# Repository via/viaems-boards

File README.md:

# viaems-boards
ViaEMS PCB Designs

In order of creation...
## Analog V1
 - Analog/ADC Core board based on a DIP TLC2543
 - All throughhole
 - Dedicated 5V supply
 - 4 Thermistor inputs
 - Inputs for EGO, BRV, MAP, TPS
 - 5 Spares

## IO V1
 - IO core board
 - 4x ignition outputs
 - 6x Low side drivers
 - CAN driver
 - Digital inputs

Do not use because:
 - 3v supply for CAN doesn't work at all
 - the FETs without gate drivers has poor performance from a 3.3 V
   microcontroller
 - No VR inputs

## Viaems V1
Original all-in-one board for ViaEMS
 - STM32F407VGT
 - 8x Low side outputs (fed by gate drivers)
 - 4x ignition outputs
 - 2x High side drivers
 - Dedicated MAP and AAP sensors on-board
 - AD7888 SPI ADC with thermistor and core inputs, one spare
 - CAN driver

Shouldn't be used anymore, but really only because the outputs chosen for test
trigger vs real triggers are different in firmware.  The board can be used
again with some minor tweaks (and I have used this board for years)

## Analog V2
Experiment board to prototype use of the MAX11632, and some knock sensing
equipment.  The ADC samples fast enough to dedicate two inputs to knock sensing,
which uses an op amp input filter.  Provides core inputs, a dedicated MAP
sensor, and an additional 8 spare inputs.

The board works fine, but I'm unlikely to commit to the MAX11632: since it seems
incredibly finicky with SPI noise, and it doesn't provide a good way to know if
there is an issue. It requires a setup command.  The knock sensing filter works
great though.  Ultimately issues with this chip pushed me to investigate the
TLV2553.

Also, its way too big.

## IO V2
** Do not use! **
Simple breakout board as an upgrade to IO V2:
 - IO Core board
 - 5v supply (and fused output)
 - 4x ignition outputs
 - 8x Low Side drivers (including 4 injectors)
 - 2x Digital inputs
 - 2 VR inputs

Experiment with replacing the 2-port gate drivers with the 4-port MIC4469
 variant.  This board was made mostly to experiment with various FETs.

This board is missing inline resistors between the MIC4469 and FETs.  This is
incredibly important for the VND7NV04 -- without it, the negative pulse from
injectors destroys the gate control logic and causes it to latch partly on.

Ultimately this board is also *way* too big.

## Analog V3
Another experiment, this time for the TI TLV2553.  This ADC has only 11 inputs,
and samples at 200kHz (vs 300 kHz of the MAX11632).  However, its control is
identical to the TLC2543, which has self test functionality.  It is still fast
enough to allow for two inputs to be sampled at 40 kHz (and the rest at 10 kHz).
 - Analog Core board based on TLV2553
 - Small form factor (78x34 mm)
 - 2x SPI headers to make debugging easier
 - dedicated 5v supply (and fused output)
 - 1x MAP input
 - 2x knock sensor inputs
 - 3x Spare inputs

 I decided (after the fact) to make all the other boards the same form factor

## LSD V1 (Split from IO V2)
The full contents of IO V2 could not fit on a single 78x34 board, so it is split
into two -- one for the low side drivers, one for everything else.  Other
lessons learned from IO V2 were to add gate resistors for the FETs, and that
indicator LEDs are worth the effort to plan into the design.
 - Low side/Injector Core board
 - Small form factor (78x34)
 - 4x Injector outputs
 - 4x LSD outputs (or an extra 4x injectors)
 - Indicator LEDs

## Pwr-Ign-V1 (Split from IO V2)
An upgrade from IO V2, with gate resistors fixed, indicator LEDs on all outputs
and trigger inputs
 - 5v supply
 - 2x VR inputs
 - 2x Digital inputs
 - 4x Ignition outputs

## Proto-stm32f427 (v2)
Generic testing board for stm32f427 or gd32f470.  This is the same pcb
dimensions as the prior 3 boards, and comes with:
 - 100 LQFP footprint for microcontroller
 - USB Type-C (with FS-only pinout)
 - Optional soic-8 spi nor flash footprint on SPI1
 - Full 20 pin SWD+ETM trace connector

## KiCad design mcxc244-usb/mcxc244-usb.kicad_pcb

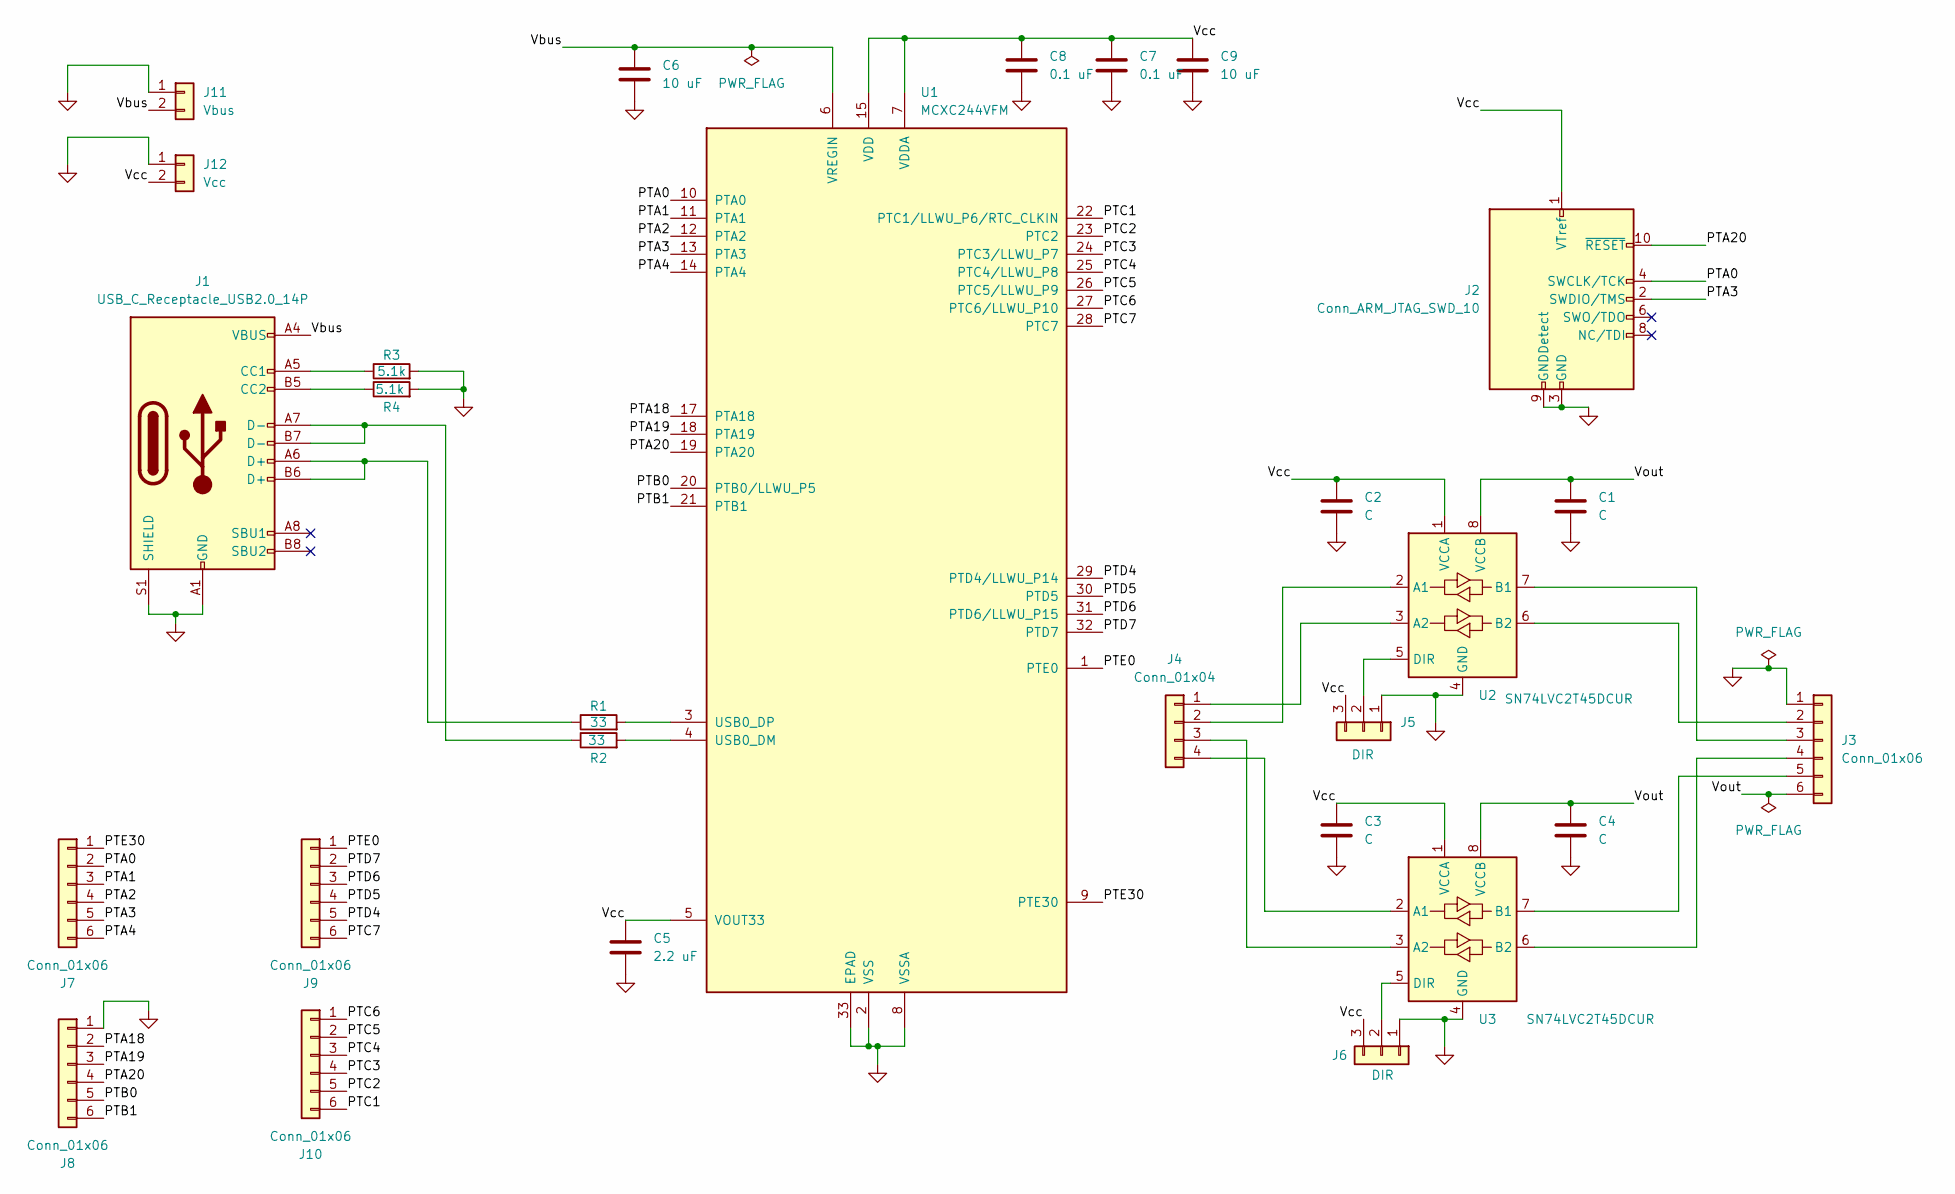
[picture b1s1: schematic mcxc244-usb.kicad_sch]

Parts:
C1, C2, C3, C4: C; C_0805_2012Metric
C5: 2.2 uF; C_0805_2012Metric
C6, C9: 10 uF; C_0805_2012Metric
C7, C8: 0.1 uF; C_0805_2012Metric
J1: USB_C_Receptacle_USB2.0_14P; USB_C_Receptacle_GCT_USB4105-xx-A_16P_TopMnt_Horizontal
J2: Conn_ARM_JTAG_SWD_10; PinHeader_2x05_P1.27mm_Vertical_SMD
J3, J7, J8, J9, J10: Conn_01x06; PinHeader_1x06_P2.54mm_Vertical
J4: Conn_01x04; PinHeader_1x04_P2.54mm_Vertical
J5, J6: DIR; PinHeader_1x03_P2.54mm_Vertical
J11: Vbus; PinHeader_1x02_P2.54mm_Vertical
J12: Vcc; PinHeader_1x02_P2.54mm_Vertical
R1, R2: 33; R_0805_2012Metric
R3, R4: 5.1k; R_0805_2012Metric
U1: MCXC244VFM; QFN-32-1EP_5x5mm_P0.5mm_EP3.45x3.45mm
U2, U3: SN74LVC2T45DCUR; VSSOP-8_2.3x2mm_P0.5mm

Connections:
/PTA0: J2.4 (SWCLK/TCK), J7.2, U1.10 (PTA0)
/PTA1: J7.3, U1.11 (PTA1)
/PTA2: J7.4, U1.12 (PTA2)
/PTA3: J2.2 (SWDIO/TMS), J7.5, U1.13 (PTA3)
/PTA4: J7.6, U1.14 (PTA4)
/PTA18: J8.2, U1.17 (PTA18)
/PTA19: J8.3, U1.18 (PTA19)
/PTA20: J2.10 (~RESET), J8.4, U1.19 (PTA20)
/PTB0: J8.5, U1.20 (PTB0/LLWU_P5)
/PTB1: J8.6, U1.21 (PTB1)
/PTC1: J10.6, U1.22 (PTC1/LLWU_P6/RTC_CLKIN)
/PTC2: J10.5, U1.23 (PTC2)
/PTC3: J10.4, U1.24 (PTC3/LLWU_P7)
/PTC4: J10.3, U1.25 (PTC4/LLWU_P8)
/PTC5: J10.2, U1.26 (PTC5/LLWU_P9)
/PTC6: J10.1, U1.27 (PTC6/LLWU_P10)
/PTC7: J9.6, U1.28 (PTC7)
/PTD4: J9.5, U1.29 (PTD4/LLWU_P14)
/PTD5: J9.4, U1.30 (PTD5)
/PTD6: J9.3, U1.31 (PTD6/LLWU_P15)
/PTD7: J9.2, U1.32 (PTD7)
/PTE0: J9.1, U1.1 (PTE0)
/PTE30: J7.1, U1.9 (PTE30)
/Vbus: C6.1, J1.A4 (VBUS), J1.A9 (VBUS), J1.B4 (VBUS), J1.B9 (VBUS), J11.2, U1.6 (VREGIN)
/Vcc: C2.1, C3.1, C5.1, C7.1, C8.1, C9.1, J2.1 (VTref), J5.3, J6.3, J12.2, U1.5 (VOUT33), U1.7 (VDDA), U1.15 (VDD), U2.1 (VCCA), U3.1 (VCCA)
/Vout: C1.1, C4.1, J3.6, U2.8 (VCCB), U3.8 (VCCB)
GND: C1.2, C2.2, C3.2, C4.2, C5.2, C6.2, C7.2, C8.2, C9.2, J1.A1 (GND), J1.A12 (GND), J1.B1 (GND), J1.B12 (GND), J1.S1 (SHIELD), J2.3 (GND), J2.5 (GND), J2.9 (GNDDetect), J3.1, J5.1, J6.1, J8.1, J11.1, J12.1, R3.2, R4.2, U1.2 (VSS), U1.8 (VSSA), U1.16 (VSS), U1.33 (EPAD), U2.4 (GND), U3.4 (GND)
unnamed: J1.A5 (CC1), R3.1
unnamed: J1.B5 (CC2), R4.1
unnamed: J1.A6 (D+), J1.B6 (D+), R1.1
unnamed: J1.A7 (D-), J1.B7 (D-), R2.1
unnamed: J3.2, U2.6 (B2)
unnamed: J3.3, U2.7 (B1)
unnamed: J3.4, U3.6 (B2)
unnamed: J3.5, U3.7 (B1)
unnamed: J4.1, U2.3 (A2)
unnamed: J4.2, U2.2 (A1)
unnamed: J4.3, U3.3 (A2)
unnamed: J4.4, U3.2 (A1)
unnamed: J5.2, U2.5 (DIR)
unnamed: J6.2, U3.5 (DIR)
unnamed: R2.2, U1.4 (USB0_DM)
unnamed: R1.2, U1.3 (USB0_DP)

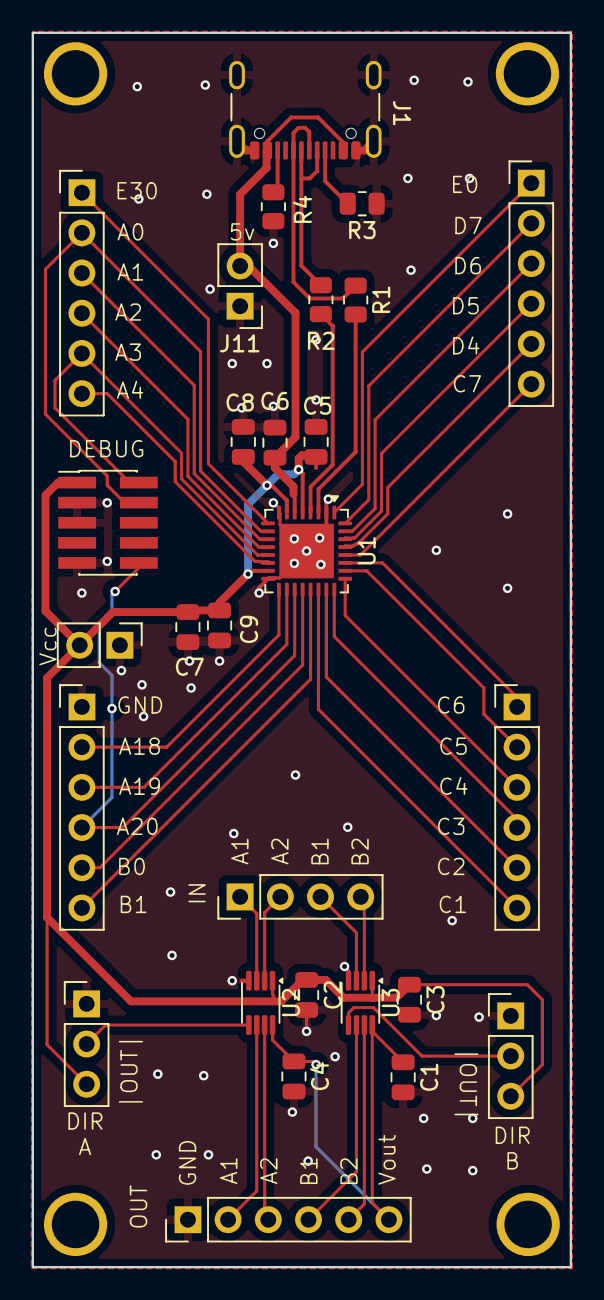
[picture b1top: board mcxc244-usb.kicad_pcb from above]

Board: 2 copper layers, 34.0 x 78.0 mm, 28 parts (0 on the bottom side), 43 nets.

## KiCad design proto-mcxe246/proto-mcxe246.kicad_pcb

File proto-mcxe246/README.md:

Power schemes:
 - USB Power -> 5v Vdd    (3.3v Reg powering uart)
 - USB Power -> 3v3 Vdd
 - SWD 3.3 V power -> 3v3 Vdd.  Uart?  Only if 5vusb jumpered.
 -

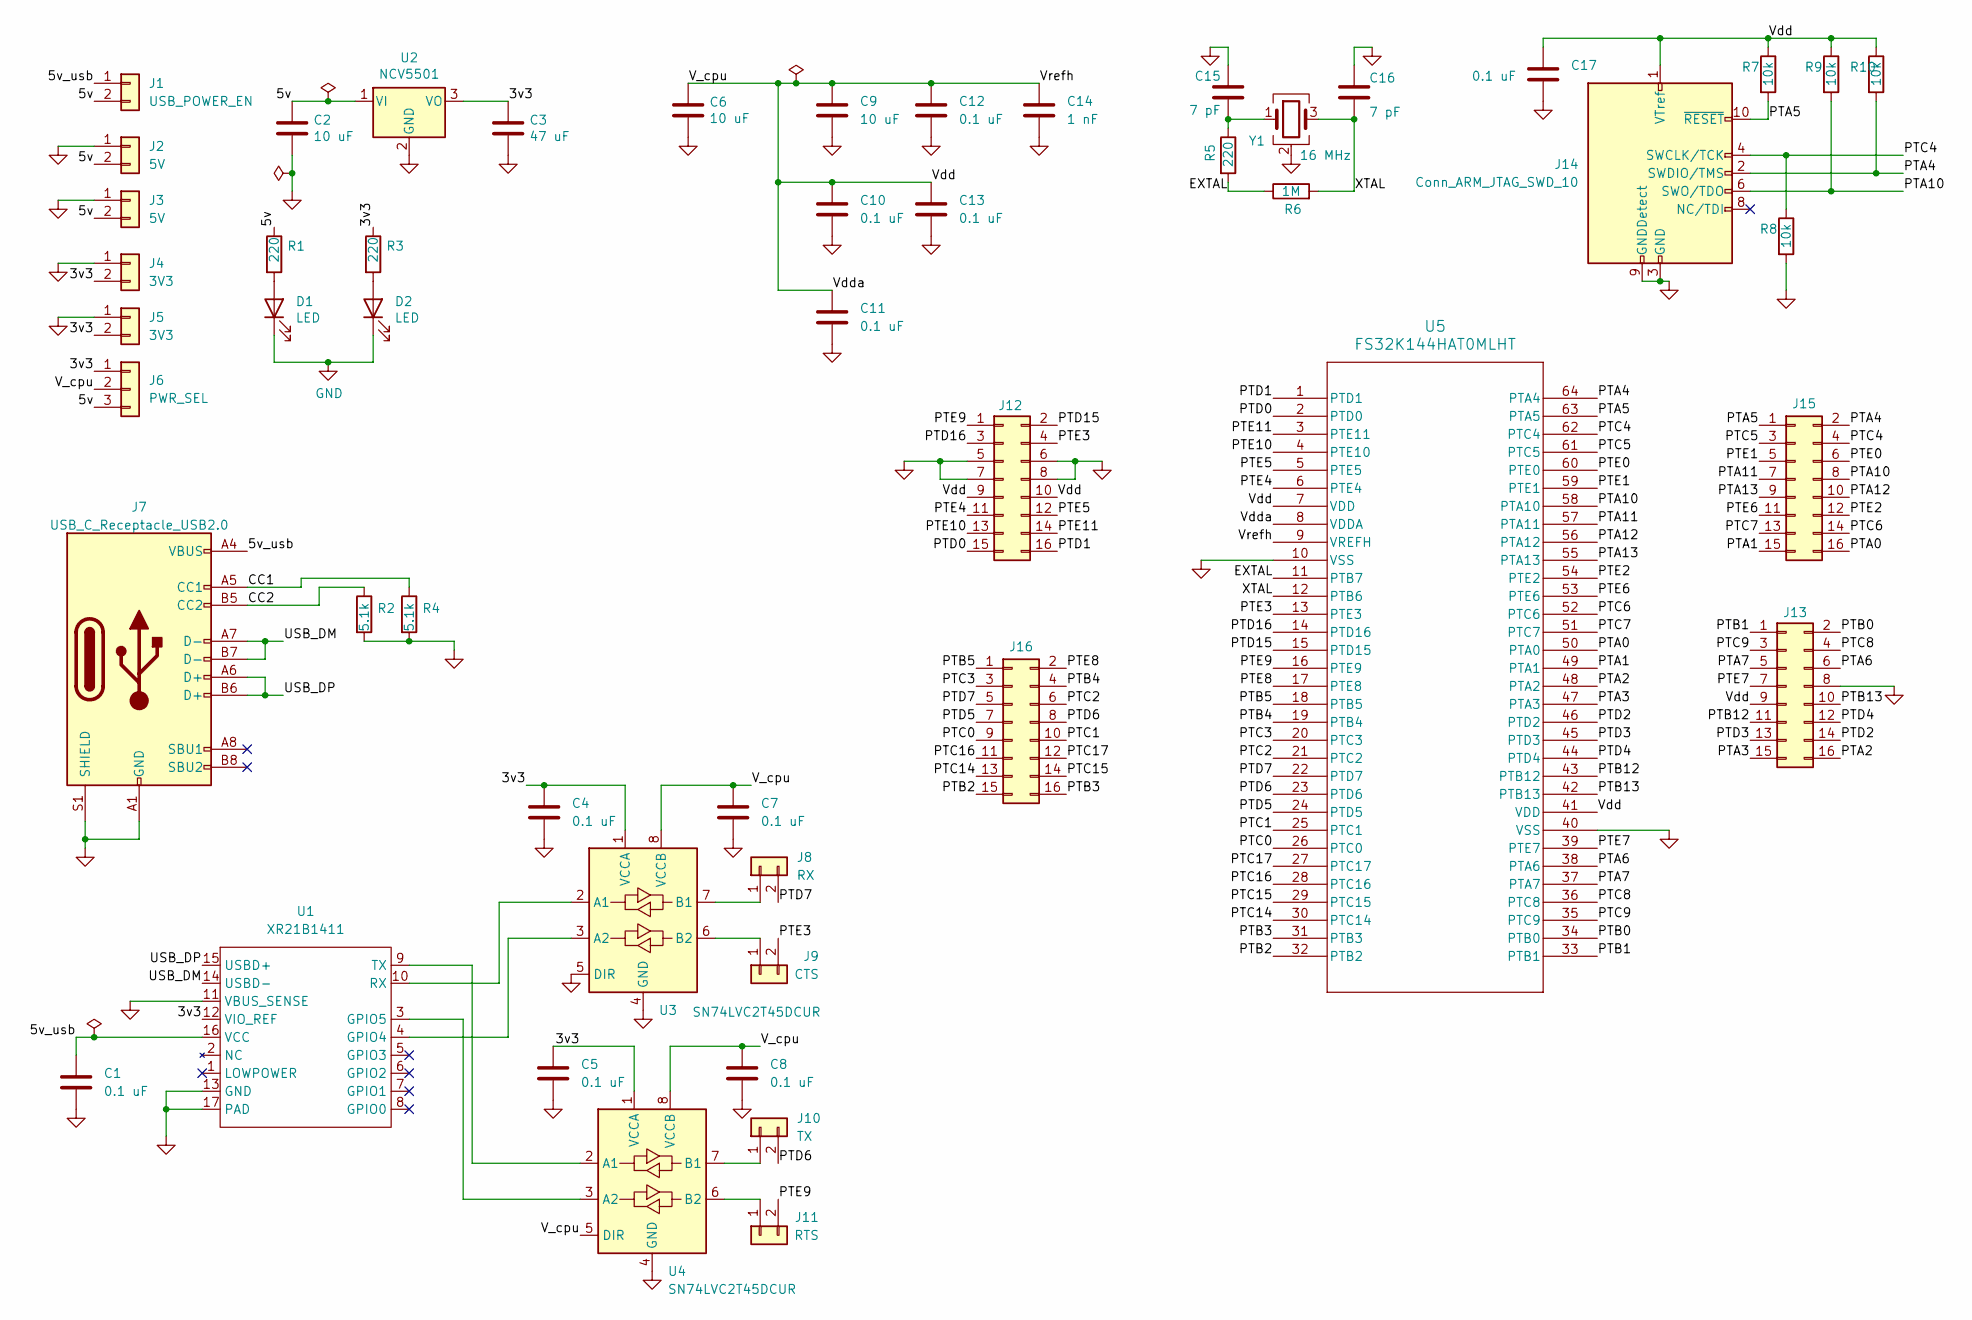
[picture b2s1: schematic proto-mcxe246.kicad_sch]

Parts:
C1, C4, C5, C7, C8, C10, C11, C12, C13, C17: 0.1 uF; C_0805_2012Metric_Pad1.18x1.45mm_HandSolder
C2: 10 uF; C_0805_2012Metric_Pad1.18x1.45mm_HandSolder; Digikey-Part 587-3417-1-ND
C3: 47 uF; C_0805_2012Metric_Pad1.18x1.45mm_HandSolder; Digikey-Part 718-1608-1-ND
C6: 10 uF; C_0805_2012Metric_Pad1.18x1.45mm_HandSolder; Digikey-Part 718-1608-1-ND
C9: 10 uF; C_0805_2012Metric_Pad1.18x1.45mm_HandSolder
C14: 1 nF; C_0805_2012Metric_Pad1.18x1.45mm_HandSolder
C15, C16: 7 pF; C_0805_2012Metric_Pad1.18x1.45mm_HandSolder
D1, D2: LED; LED_0805_2012Metric_Pad1.15x1.40mm_HandSolder; Digikey-Part 475-1415-1-ND
J1: USB_POWER_EN; PinHeader_1x02_P2.54mm_Vertical
J2, J3: 5V; PinHeader_1x02_P2.54mm_Vertical
J4, J5: 3V3; PinHeader_1x02_P2.54mm_Vertical
J6: PWR_SEL; PinHeader_1x03_P2.54mm_Vertical
J7: USB_C_Receptacle_USB2.0; USB_C_Receptacle_GCT_USB4105-xx-A_16P_TopMnt_Horizontal; Digikey-Part 2073-USB4105-GF-ACT-ND
J8: RX; PinHeader_1x02_P2.54mm_Vertical
J9: CTS; PinHeader_1x02_P2.54mm_Vertical
J10: TX; PinHeader_1x02_P2.54mm_Vertical
J11: RTS; PinHeader_1x02_P2.54mm_Vertical
J12, J13, J15, J16: Conn_02x08_Odd_Even; PinHeader_2x08_P2.54mm_Vertical
J14: Conn_ARM_JTAG_SWD_10; PinHeader_2x05_P1.27mm_Vertical_SMD
R1, R3: 220; R_0805_2012Metric_Pad1.20x1.40mm_HandSolder; Digikey-Part A129741CT-ND
R2, R4: 5.1k; R_0805_2012Metric_Pad1.20x1.40mm_HandSolder
R5: 220; R_0805_2012Metric_Pad1.20x1.40mm_HandSolder
R6: 1M; R_0805_2012Metric_Pad1.20x1.40mm_HandSolder
R7, R8, R9, R10: 10k; R_0805_2012Metric_Pad1.20x1.40mm_HandSolder
U1: XR21B1411; QFN-16-1EP_3x3mm_P0.5mm_EP1.7x1.7mm
U2: NCV5501; TO-252-2; Digikey-Part NCV5501DT33GOS-ND
U3, U4: SN74LVC2T45DCUR; VSSOP-8_2.3x2mm_P0.5mm
U5: FS32K144HAT0MLHT; SOT1699-1_LQFP64_NXP
Y1: 16 MHz; Crystal_SMD_2520-4Pin_2.5x2.0mm; Digikey-Part 535-13361-1-ND -

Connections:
/3v3: C3.1, C4.1, C5.1, J4.2, J5.2, J6.1, R3.1, U1.12 (VIO_REF), U2.3 (VO), U3.1 (VCCA), U4.1 (VCCA)
/5v: C2.1, J1.2, J2.2, J3.2, J6.3, R1.1, U2.1 (VI)
/5v_usb: C1.1, J1.1, J7.A4 (VBUS), J7.A9 (VBUS), J7.B4 (VBUS), J7.B9 (VBUS), U1.16 (VCC)
/CC1: J7.A5 (CC1), R4.1
/CC2: J7.B5 (CC2), R2.1
/EXTAL: R5.2, R6.1, U5.11 (PTB7)
/PTA0: J15.16, U5.50 (PTA0)
/PTA1: J15.15, U5.49 (PTA1)
/PTA2: J13.16, U5.48 (PTA2)
/PTA3: J13.15, U5.47 (PTA3)
/PTA4: J14.2 (SWDIO/TMS), J15.2, R10.2, U5.64 (PTA4)
/PTA5: J14.10 (~RESET), J15.1, R7.2, U5.63 (PTA5)
/PTA6: J13.6, U5.38 (PTA6)
/PTA7: J13.5, U5.37 (PTA7)
/PTA10: J14.6 (SWO/TDO), J15.8, R9.2, U5.58 (PTA10)
/PTA11: J15.7, U5.57 (PTA11)
/PTA12: J15.10, U5.56 (PTA12)
/PTA13: J15.9, U5.55 (PTA13)
/PTB0: J13.2, U5.34 (PTB0)
/PTB1: J13.1, U5.33 (PTB1)
/PTB2: J16.15, U5.32 (PTB2)
/PTB3: J16.16, U5.31 (PTB3)
/PTB4: J16.4, U5.19 (PTB4)
/PTB5: J16.1, U5.18 (PTB5)
/PTB12: J13.11, U5.43 (PTB12)
/PTB13: J13.10, U5.42 (PTB13)
/PTC0: J16.9, U5.26 (PTC0)
/PTC1: J16.10, U5.25 (PTC1)
/PTC2: J16.6, U5.21 (PTC2)
/PTC3: J16.3, U5.20 (PTC3)
/PTC4: J14.4 (SWCLK/TCK), J15.4, R8.1, U5.62 (PTC4)
/PTC5: J15.3, U5.61 (PTC5)
/PTC6: J15.14, U5.52 (PTC6)
/PTC7: J15.13, U5.51 (PTC7)
/PTC8: J13.4, U5.36 (PTC8)
/PTC9: J13.3, U5.35 (PTC9)
/PTC14: J16.13, U5.30 (PTC14)
/PTC15: J16.14, U5.29 (PTC15)
/PTC16: J16.11, U5.28 (PTC16)
/PTC17: J16.12, U5.27 (PTC17)
/PTD0: J12.15, U5.2 (PTD0)
/PTD1: J12.16, U5.1 (PTD1)
/PTD2: J13.14, U5.46 (PTD2)
/PTD3: J13.13, U5.45 (PTD3)
/PTD4: J13.12, U5.44 (PTD4)
/PTD5: J16.7, U5.24 (PTD5)
/PTD6: J10.2, J16.8, U5.23 (PTD6)
/PTD7: J8.2, J16.5, U5.22 (PTD7)
/PTD15: J12.2, U5.15 (PTD15)
/PTD16: J12.3, U5.14 (PTD16)
/PTE0: J15.6, U5.60 (PTE0)
/PTE1: J15.5, U5.59 (PTE1)
/PTE2: J15.12, U5.54 (PTE2)
/PTE3: J9.2, J12.4, U5.13 (PTE3)
/PTE4: J12.11, U5.6 (PTE4)
/PTE5: J12.12, U5.5 (PTE5)
/PTE6: J15.11, U5.53 (PTE6)
/PTE7: J13.7, U5.39 (PTE7)
/PTE8: J16.2, U5.17 (PTE8)
/PTE9: J11.2, J12.1, U5.16 (PTE9)
/PTE10: J12.13, U5.4 (PTE10)
/PTE11: J12.14, U5.3 (PTE11)
/USB_DM: J7.A7 (D-), J7.B7 (D-), U1.14 (USBD-)
/USB_DP: J7.A6 (D+), J7.B6 (D+), U1.15 (USBD+)
/V_cpu: C6.1, C7.1, C8.1, C9.1, C10.1, C11.1, C12.1, C13.1, C14.1, C17.1, J6.2, J12.9, J12.10, J13.9, J14.1 (VTref), R7.1, R9.1, R10.1, U3.8 (VCCB), U4.5 (DIR), U4.8 (VCCB), U5.7 (VDD), U5.8 (VDDA), U5.9 (VREFH), U5.41 (VDD)
/XTAL: C16.2, R6.2, U5.12 (PTB6), Y1.3
GND: C1.2, C2.2, C3.2, C4.2, C5.2, C6.2, C7.2, C8.2, C9.2, C10.2, C11.2, C12.2, C13.2, C14.2, C15.1, C16.1, C17.2, D1.1 (K), D2.1 (K), J2.1, J3.1, J4.1, J5.1, J7.A1 (GND), J7.A12 (GND), J7.B1 (GND), J7.B12 (GND), J7.S1 (SHIELD), J12.5, J12.6, J12.7, J12.8, J13.8, J14.3 (GND), J14.5 (GND), J14.9 (GNDDetect), R2.2, R4.2, R8.2, U1.11 (VBUS_SENSE), U1.13 (GND), U1.17 (PAD), U2.2 (GND), U3.4 (GND), U3.5 (DIR), U4.4 (GND), U5.10 (VSS), U5.40 (VSS), Y1.2 (G), Y1.4 (G)
unnamed: C15.2, R5.1, Y1.1
unnamed: D1.2 (A), R1.2
unnamed: D2.2 (A), R3.2
unnamed: J8.1, U3.7 (B1)
unnamed: J9.1, U3.6 (B2)
unnamed: J10.1, U4.7 (B1)
unnamed: J11.1, U4.6 (B2)
unnamed: U1.4 (GPIO4), U3.3 (A2)
unnamed: U1.3 (GPIO5), U4.3 (A2)
unnamed: U1.10 (RX), U3.2 (A1)
unnamed: U1.9 (TX), U4.2 (A1)

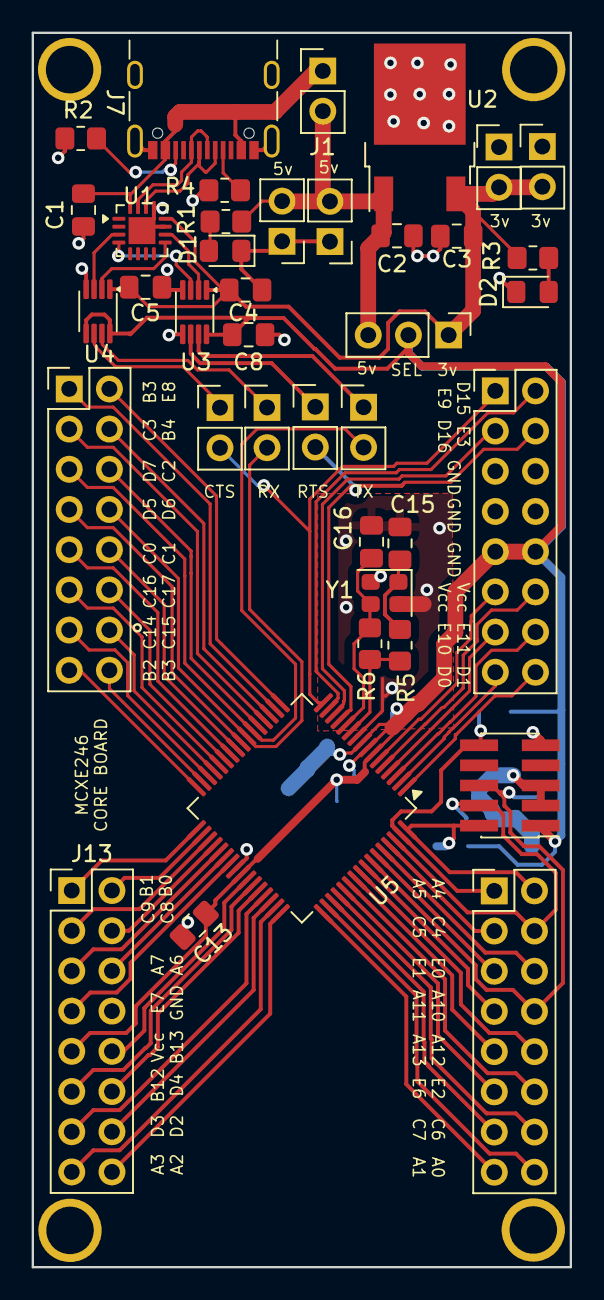
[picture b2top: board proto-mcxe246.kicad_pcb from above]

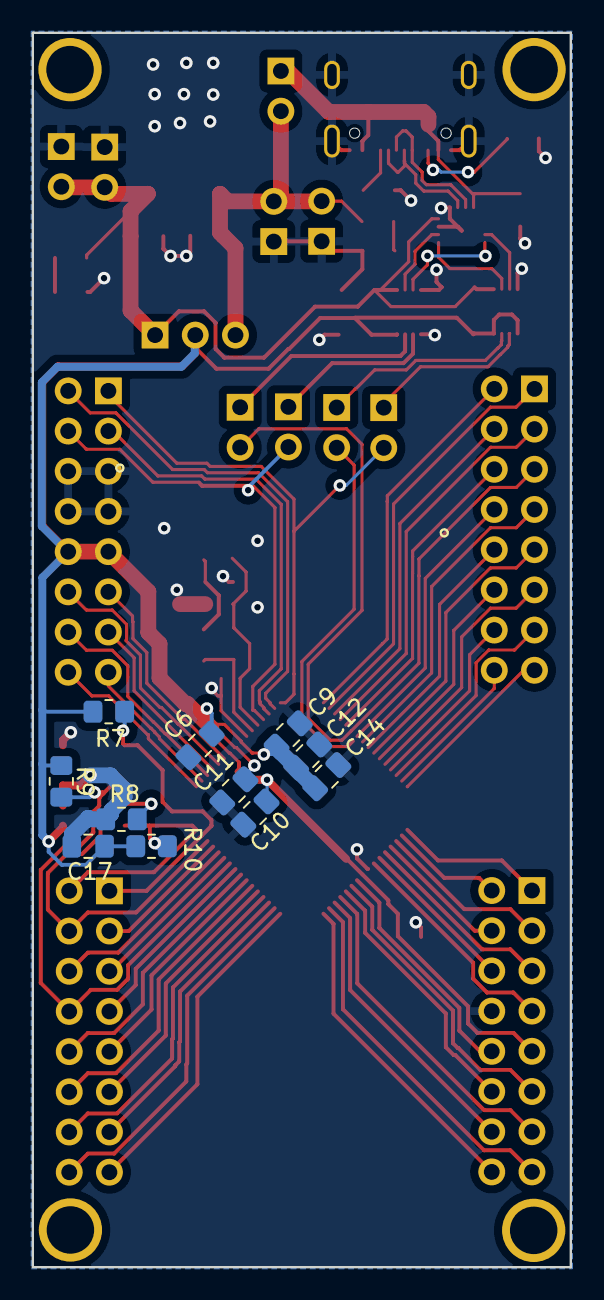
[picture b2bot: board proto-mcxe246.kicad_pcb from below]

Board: 2 copper layers, 34.0 x 78.0 mm, 50 parts (11 on the bottom side), 78 nets.

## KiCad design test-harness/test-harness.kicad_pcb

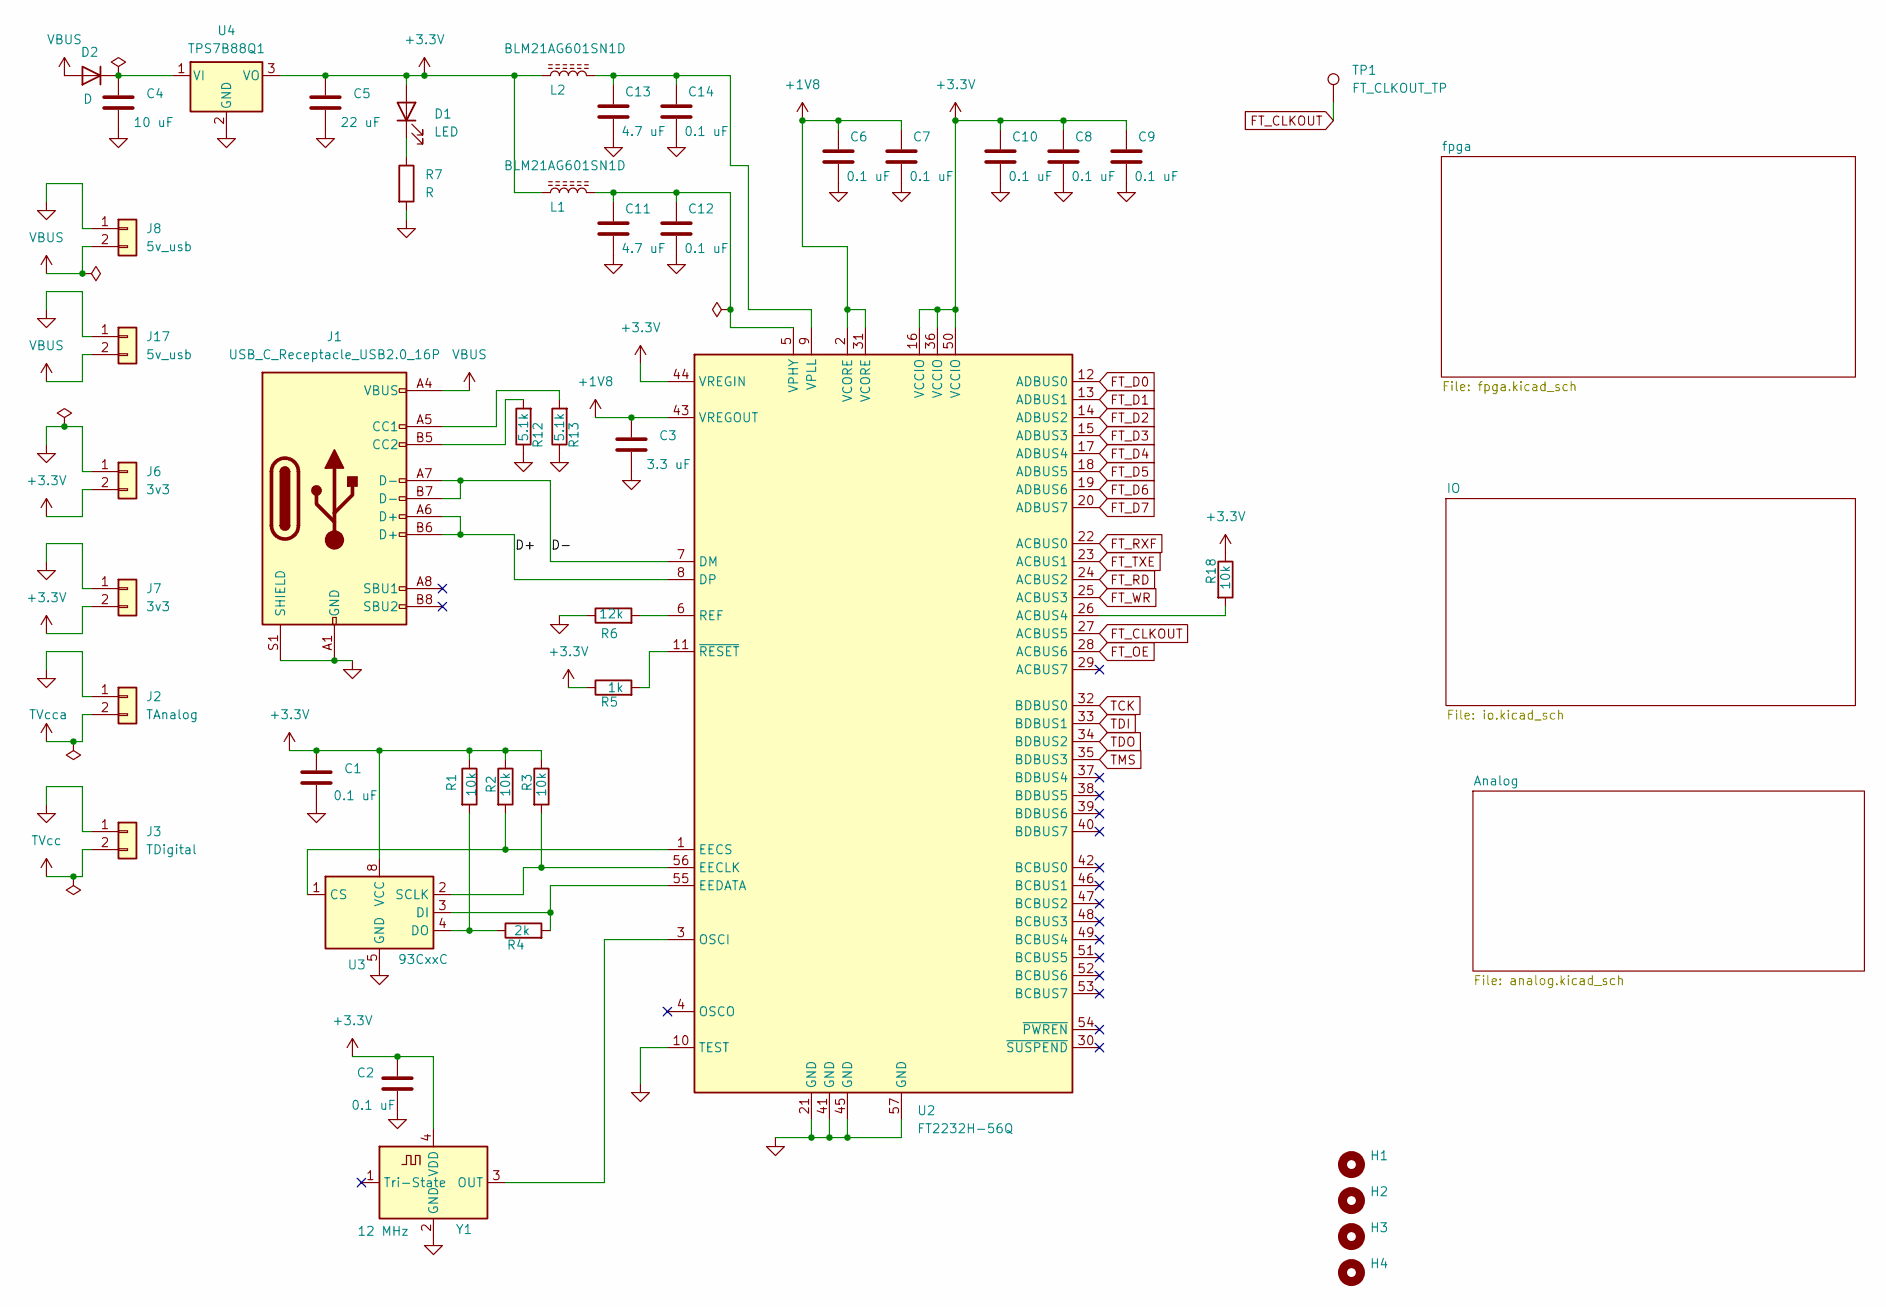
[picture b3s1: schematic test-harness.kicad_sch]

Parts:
C1, C2, C6, C7, C8, C9, C10, C12, C14: 0.1 uF; C_0805_2012Metric
C3: 3.3 uF; C_0805_2012Metric
C4: 10 uF; C_0805_2012Metric
C5: 22 uF; C_0805_2012Metric
C11, C13: 4.7 uF; C_0805_2012Metric
D1: LED; LED_0805_2012Metric
D2: D; D_0805_2012Metric; Digikey-Part 478-7800-1-ND
H1, H2, H3, H4: MountingHole; MountingHole_2.5mm_Pad
J1: USB_C_Receptacle_USB2.0_16P; USB_C_Receptacle_GCT_USB4105-xx-A_16P_TopMnt_Horizontal
J2: TAnalog; PinHeader_1x02_P2.54mm_Vertical
J3: TDigital; PinHeader_1x02_P2.54mm_Vertical
J6, J7: 3v3; PinHeader_1x02_P2.54mm_Vertical
J8, J17: 5v_usb; PinHeader_1x02_P2.54mm_Vertical
L1, L2: BLM21AG601SN1D; L_0805_2012Metric; Digikey-Part 490-1040-1-ND
R1, R2, R3, R18: 10k; R_0805_2012Metric
R4: 2k; R_0805_2012Metric
R5: 1k; R_0805_2012Metric
R6: 12k; R_0805_2012Metric
R7: R; R_0805_2012Metric
R12, R13: 5.1k; R_0805_2012Metric
TP1: FT_CLKOUT_TP; TestPoint_Pad_D1.5mm
U2: FT2232H-56Q; QFN-56-1EP_8x8mm_P0.5mm_EP5.9x5.9mm; Digikey-Part 768-1276-ND
U3: 93CxxC; SOIC-8_3.9x4.9mm_P1.27mm; Digikey-Part 93LC56BT-I/SNCT-ND
U4: TPS7B88Q1; TO-252-2; Digikey-Part 296-TPS7B8833QKVURQ1R2CT-ND
Y1: 12 MHz; Oscillator_SMD_ECS_2520MV-xxx-xx-4Pin_2.5x2.0mm; Digikey-Part 50-ECS-2520SMVQ-120-DS-TRCT-ND

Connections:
+1V8: C3.1, C6.1, C7.1, U2.2 (VCORE), U2.31 (VCORE), U2.43 (VREGOUT)
+3.3V: C1.1, C2.1, C5.1, C8.1, C9.1, C10.1, D1.2 (A), J6.2, J7.2, L1.1, L2.1, R1.1, R2.1, R3.1, R5.1, R18.1, U2.16 (VCCIO), U2.36 (VCCIO), U2.44 (VREGIN), U2.50 (VCCIO), U3.8 (VCC), U4.3 (VO), Y1.4 (VDD); also elsewhere on the board
/D+: J1.A6 (D+), J1.B6 (D+), U2.8 (DP)
/D-: J1.A7 (D-), J1.B7 (D-), U2.7 (DM)
FT_CLKOUT: TP1.1, U2.27 (ACBUS5); also elsewhere on the board
FT_D0: U2.12 (ADBUS0); also elsewhere on the board
FT_D1: U2.13 (ADBUS1); also elsewhere on the board
FT_D2: U2.14 (ADBUS2); also elsewhere on the board
FT_D3: U2.15 (ADBUS3); also elsewhere on the board
FT_D4: U2.17 (ADBUS4); also elsewhere on the board
FT_D5: U2.18 (ADBUS5); also elsewhere on the board
FT_D6: U2.19 (ADBUS6); also elsewhere on the board
FT_D7: U2.20 (ADBUS7); also elsewhere on the board
FT_OE: U2.28 (ACBUS6); also elsewhere on the board
FT_RD: U2.24 (ACBUS2); also elsewhere on the board
FT_RXF: U2.22 (ACBUS0); also elsewhere on the board
FT_TXE: U2.23 (ACBUS1); also elsewhere on the board
FT_WR: U2.25 (ACBUS3); also elsewhere on the board
GND: C1.2, C2.2, C3.2, C4.2, C5.2, C6.2, C7.2, C8.2, C9.2, C10.2, C11.2, C12.2, C13.2, C14.2, J1.A1 (GND), J1.A12 (GND), J1.B1 (GND), J1.B12 (GND), J1.S1 (SHIELD), J2.1, J3.1, J6.1, J7.1, J8.1, J17.1, R6.1, R7.2, R12.1, R13.1, U2.10 (TEST), U2.21 (GND), U2.41 (GND), U2.45 (GND), U2.57 (GND), U3.5 (GND), U4.2 (GND), Y1.2 (GND); also elsewhere on the board
unnamed: D1.1 (K), R7.1
unnamed: C4.1, D2.1 (K), U4.1 (VI)
unnamed: J1.A5 (CC1), R13.2
unnamed: J1.B5 (CC2), R12.2
unnamed: R18.2, U2.26 (ACBUS4)
unnamed: R3.2, U2.56 (EECLK), U3.2 (SCLK)
unnamed: R2.2, U2.1 (EECS), U3.1 (CS)
unnamed: R4.2, U2.55 (EEDATA), U3.3 (DI)
unnamed: U2.3 (OSCI), Y1.3 (OUT)
unnamed: R6.2, U2.6 (REF)
unnamed: C11.1, C12.1, L1.2, U2.5 (VPHY)
unnamed: C13.1, C14.1, L2.2, U2.9 (VPLL)
unnamed: R5.2, U2.11 (~RESET)
unnamed: R1.2, R4.1, U3.4 (DO)
TCK: U2.32 (BDBUS0); also elsewhere on the board
TDI: U2.33 (BDBUS1); also elsewhere on the board
TDO: U2.34 (BDBUS2); also elsewhere on the board
TMS: U2.35 (BDBUS3); also elsewhere on the board
TVcc: J3.2; also elsewhere on the board
TVcca: J2.2; also elsewhere on the board
VBUS: D2.2 (A), J1.A4 (VBUS), J1.A9 (VBUS), J1.B4 (VBUS), J1.B9 (VBUS), J8.2, J17.2

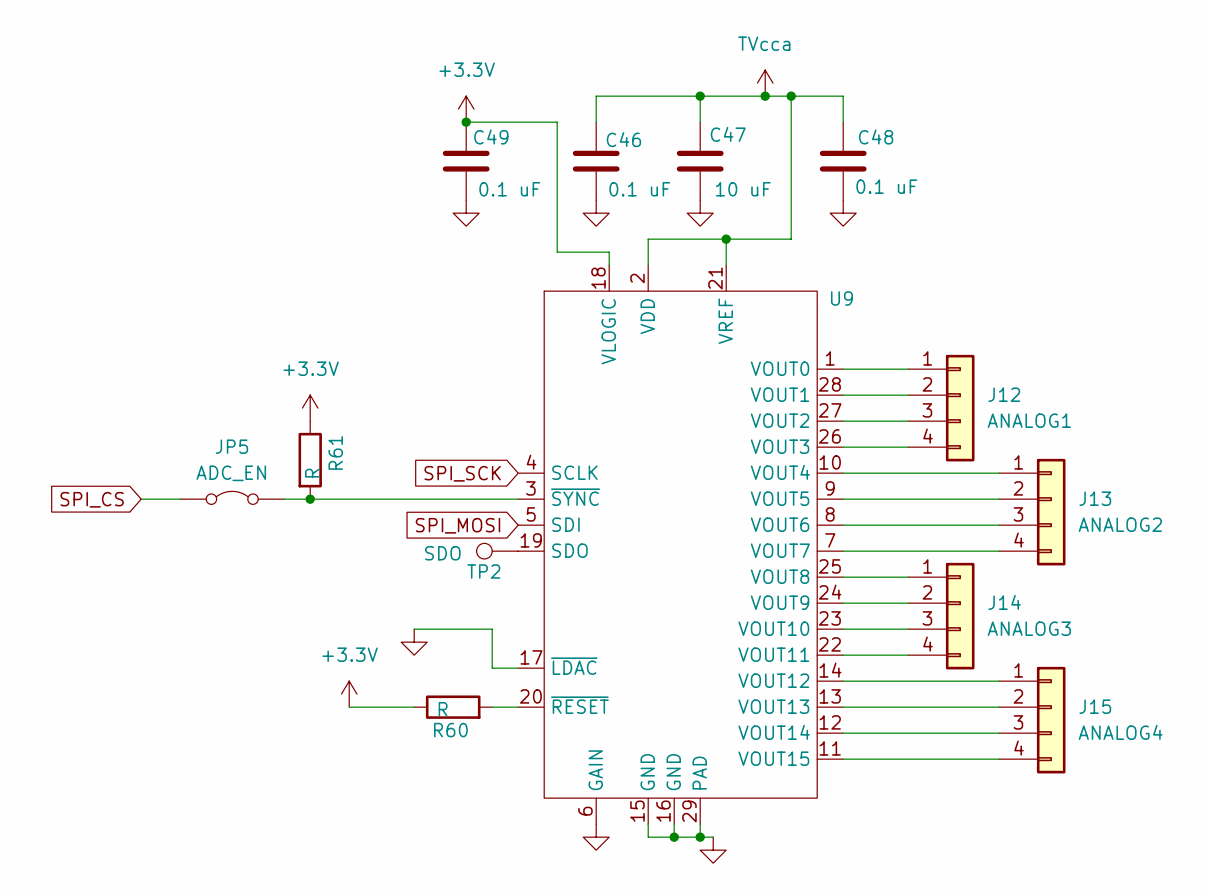
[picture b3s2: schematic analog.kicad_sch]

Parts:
C46, C48, C49: 0.1 uF; C_0805_2012Metric
C47: 10 uF; C_0805_2012Metric
J12: ANALOG1; PinHeader_1x04_P2.54mm_Vertical
J13: ANALOG2; PinHeader_1x04_P2.54mm_Vertical
J14: ANALOG3; PinHeader_1x04_P2.54mm_Vertical
J15: ANALOG4; PinHeader_1x04_P2.54mm_Vertical
JP5: ADC_EN; SolderJumper-2_P1.3mm_Open_TrianglePad1.0x1.5mm
R60, R61: R; R_0805_2012Metric
TP2: SDO; TestPoint_Pad_D1.5mm
U9: UQFN-28-1EP_4x4mm_P0.4mm_EP2.35x2.35mm_ThermalVias

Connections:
+3.3V: C49.1, R60.1, R61.1, U9.18 (VLOGIC); also elsewhere on the board
GND: C46.2, C47.2, C48.2, C49.2, U9.6 (GAIN), U9.15 (GND), U9.16 (GND), U9.17 (~LDAC), U9.29 (PAD); also elsewhere on the board
unnamed: J12.1, U9.1 (VOUT0)
unnamed: J12.2, U9.28 (VOUT1)
unnamed: J12.3, U9.27 (VOUT2)
unnamed: J12.4, U9.26 (VOUT3)
unnamed: J13.1, U9.10 (VOUT4)
unnamed: J13.2, U9.9 (VOUT5)
unnamed: J13.3, U9.8 (VOUT6)
unnamed: J13.4, U9.7 (VOUT7)
unnamed: J14.1, U9.25 (VOUT8)
unnamed: J14.2, U9.24 (VOUT9)
unnamed: J14.3, U9.23 (VOUT10)
unnamed: J14.4, U9.22 (VOUT11)
unnamed: J15.1, U9.14 (VOUT12)
unnamed: J15.2, U9.13 (VOUT13)
unnamed: J15.3, U9.12 (VOUT14)
unnamed: J15.4, U9.11 (VOUT15)
unnamed: JP5.2 (B), R61.2, U9.3 (~SYNC)
unnamed: TP2.1, U9.19 (SDO)
unnamed: R60.2, U9.20 (~RESET)
SPI_CS: JP5.1 (A); also elsewhere on the board
SPI_MOSI: U9.5 (SDI); also elsewhere on the board
SPI_SCK: U9.4 (SCLK); also elsewhere on the board
TVcca: C46.1, C47.1, C48.1, U9.2 (VDD), U9.21 (VREF); also elsewhere on the board
